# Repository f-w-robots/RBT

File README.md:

#### Installation
  - Install Arduino IDE 1.6.7+
  - To work with esp8266, install "Arduino core for ESP8266 WiFi chip", [2.3](https://github.com/esp8266/Arduino)
  - Libraries
    - [ArduinoWebSockets, our fork](https://github.com/f-w-robots/arduinoWebSockets)
    - [Arduino-IRremote](https://github.com/z3t0/Arduino-IRremote)
    - [MFRC522](https://github.com/miguelbalboa/rfid)

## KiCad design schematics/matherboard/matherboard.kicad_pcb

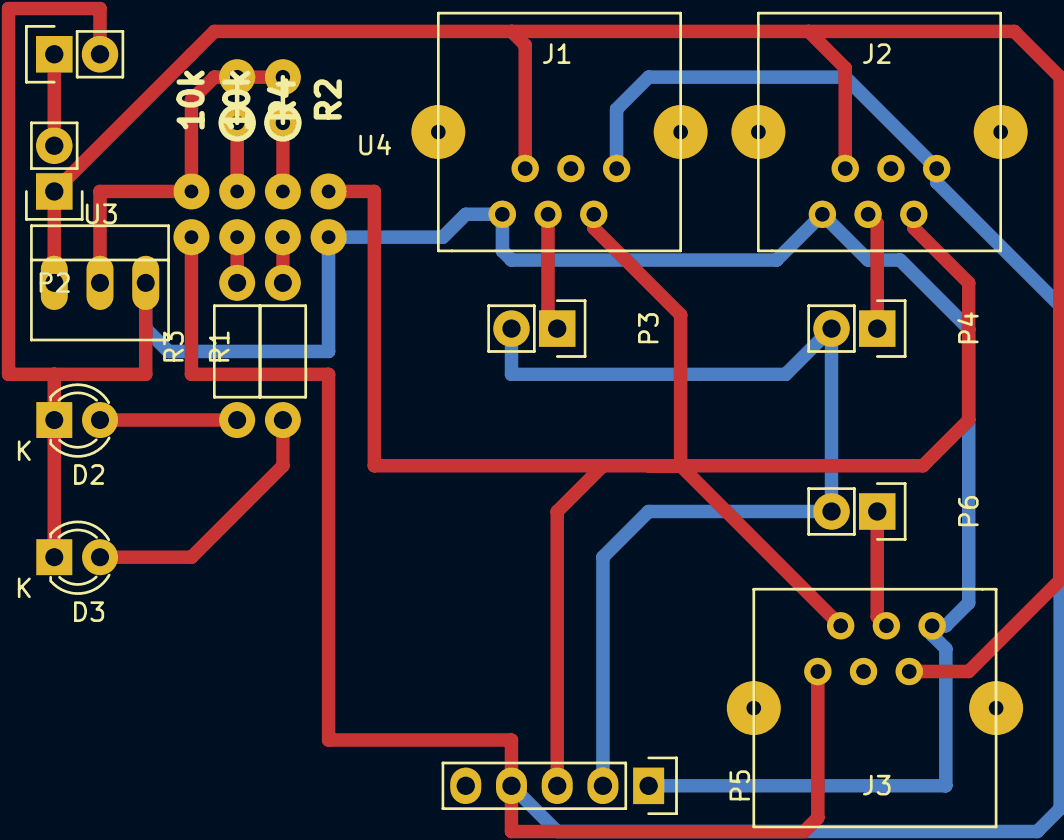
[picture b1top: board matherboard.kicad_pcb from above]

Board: 2 copper layers, 17 parts (0 on the bottom side), 16 nets.

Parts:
D2, D3: LED; LED-3MM
J1, J2, J3: RJ12; RJ12_E
P1: VCC/GND; Pin_Header_Straight_1x02
P2, P3, P4, P6: CONN_01X02; Pin_Header_Straight_1x02
P5: CONN_01X05; Pin_Header_Straight_1x05
R1, R3: 1k; Resistor_Horizontal_RM7mm
R2, R4: 10k; rc03_vert
U3: STAB3.3; PINHEAD1-3
U4: ESP8266; esp8266

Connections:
unnamed: D2.1, D3.1, J1.6, J2.6, J3.6, P1.2, P5.1, U3.3, U4.5
unnamed: D2.2, R3.1
unnamed: D3.2, R1.1
unnamed: J1.1, J2.1, J3.1, P5.4, U4.8
unnamed: J1.2, J2.2, J3.2, P5.3, U4.4
unnamed: J1.4, P3.1
unnamed: J1.5, J2.5, J3.5, P2.1, U3.1
unnamed: J2.4, P4.1
unnamed: J3.4, P6.1
unnamed: P1.1, P2.2
unnamed: P3.2, P4.2, P5.2, P6.2
unnamed: R1.2, U4.6
unnamed: R2.1, U4.3
unnamed: R2.2, R4.2, U3.2, U4.1
unnamed: R3.2, U4.7
unnamed: R4.1, U4.2

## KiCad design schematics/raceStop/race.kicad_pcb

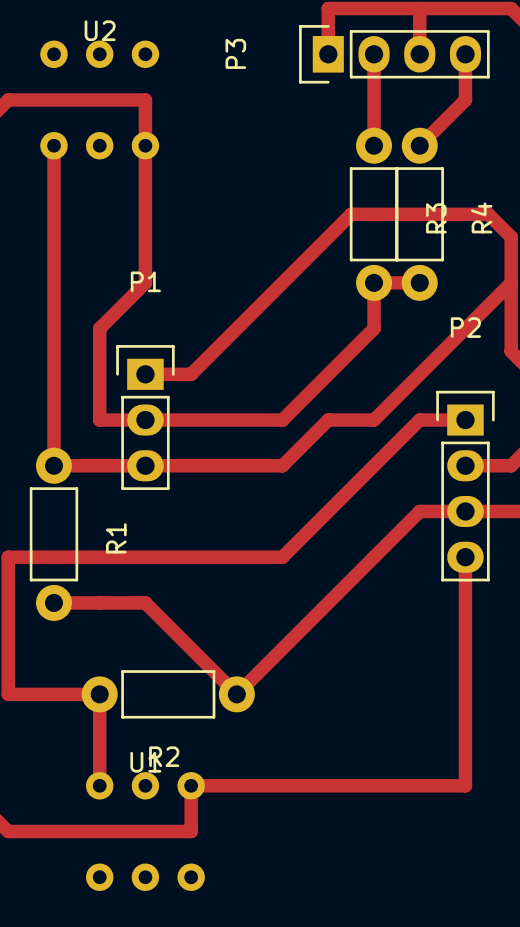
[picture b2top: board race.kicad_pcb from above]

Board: 2 copper layers, 9 parts (0 on the bottom side), 6 nets.

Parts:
P1: mass_start; Pin_Header_Straight_1x03
P2: VCC/GND/Start/Stop; Pin_Header_Straight_1x04
P3: LED; Pin_Header_Straight_1x04
R1, R2: 10k; Resistor_Horizontal_RM7mm
R3, R4: 200; Resistor_Horizontal_RM7mm
U1: STOP; button
U2: START; button

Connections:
unnamed: P1.1, P1.3, P2.2, R1.1, U2.4
unnamed: P1.2, P2.4, R3.2, R4.2, U1.3, U2.6
unnamed: P2.1, R2.2, U1.1
unnamed: P2.3, P3.1, P3.3, R1.2, R2.1
unnamed: P3.2, R3.1
unnamed: P3.4, R4.1

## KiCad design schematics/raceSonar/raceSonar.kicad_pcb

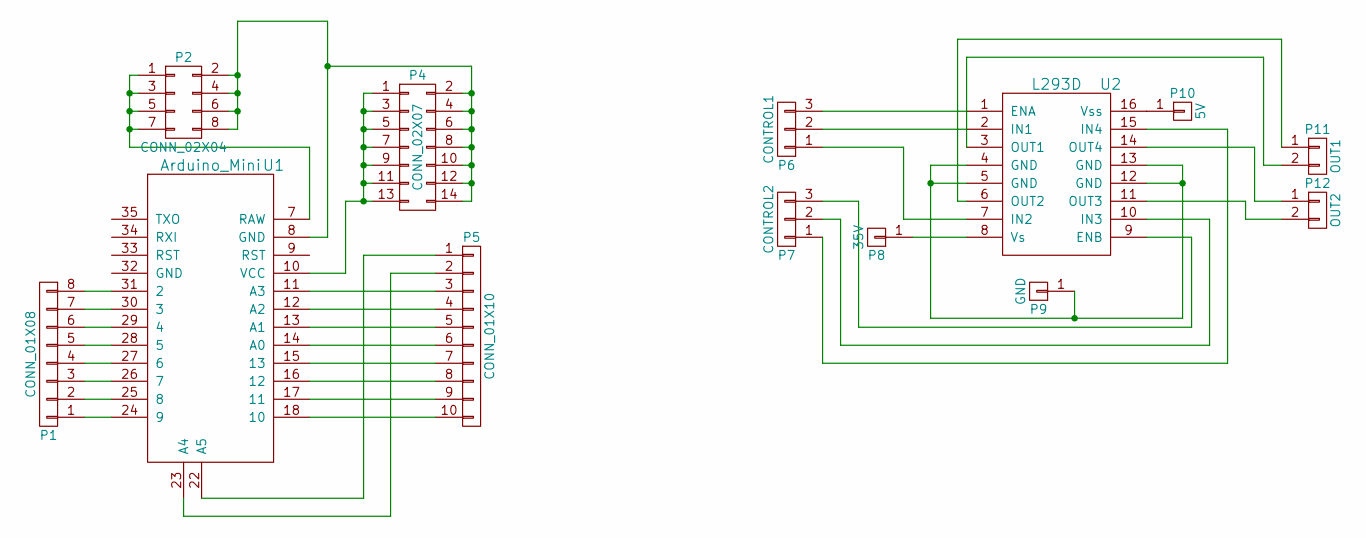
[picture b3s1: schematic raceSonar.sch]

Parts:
P1: CONN_01X08; Pin_Header_Straight_1x08
P2: CONN_02X04; Pin_Header_Straight_2x04
P4: CONN_02X07; Pin_Header_Straight_2x07
P5: CONN_01X10; Pin_Header_Straight_1x10
P6: CONTROL1; Pin_Header_Straight_1x03
P7: CONTROL2; Pin_Header_Straight_1x03
P8: 35V; Pin_Header_Straight_1x01
P9: GND; Pin_Header_Straight_1x01
P10: 5V; Pin_Header_Straight_1x01
P11: OUT1; Pin_Header_Straight_1x02
P12: OUT2; Pin_Header_Straight_1x02
U1: Arduino_Mini; arduino_mini_pro
U2: L293D; DIP-16_W7.62mm

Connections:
unnamed: P1.1, U1.24 (9)
unnamed: P1.2, U1.25 (8)
unnamed: P1.3, U1.26 (7)
unnamed: P1.4, U1.27 (6)
unnamed: P1.5, U1.28 (5)
unnamed: P1.6, U1.29 (4)
unnamed: P1.7, U1.30 (3)
unnamed: P1.8, U1.31 (2)
unnamed: P2.1, P2.3, P2.5, P2.7, U1.7 (RAW)
unnamed: P2.2, P2.4, P2.6, P2.8, P4.2, P4.4, P4.6, P4.8, P4.10, P4.12, P4.14, U1.8 (GND)
unnamed: P4.1, P4.3, P4.5, P4.7, P4.9, P4.11, P4.13, U1.10 (VCC)
unnamed: P5.1, U1.22 (A5)
unnamed: P5.2, U1.23 (A4)
unnamed: P5.3, U1.11 (A3)
unnamed: P5.4, U1.12 (A2)
unnamed: P5.5, U1.13 (A1)
unnamed: P5.6, U1.14 (A0)
unnamed: P5.7, U1.15 (13)
unnamed: P5.8, U1.16 (12)
unnamed: P5.9, U1.17 (11)
unnamed: P5.10, U1.18 (10)
unnamed: P6.1, U2.7 (IN2)
unnamed: P6.2, U2.2 (IN1)
unnamed: P6.3, U2.1 (ENA)
unnamed: P7.1, U2.15 (IN4)
unnamed: P7.2, U2.10 (IN3)
unnamed: P7.3, U2.9 (ENB)
unnamed: P8.1, U2.8 (Vs)
unnamed: P9.1, U2.4 (GND), U2.5 (GND), U2.12 (GND), U2.13 (GND)
unnamed: P10.1, U2.16 (Vss)
unnamed: P11.1, U2.6 (OUT2)
unnamed: P11.2, U2.3 (OUT1)
unnamed: P12.1, U2.14 (OUT4)
unnamed: P12.2, U2.11 (OUT3)

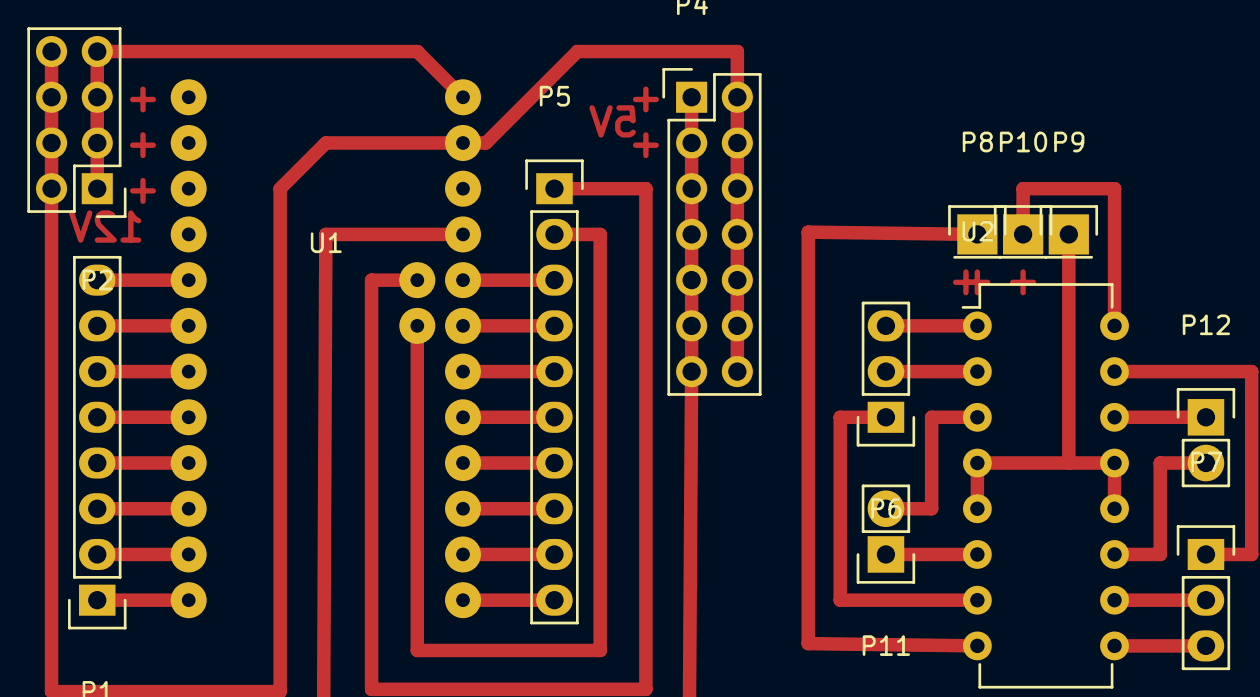
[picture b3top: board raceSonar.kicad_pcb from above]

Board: 2 copper layers, 13 parts (0 on the bottom side), 34 nets.

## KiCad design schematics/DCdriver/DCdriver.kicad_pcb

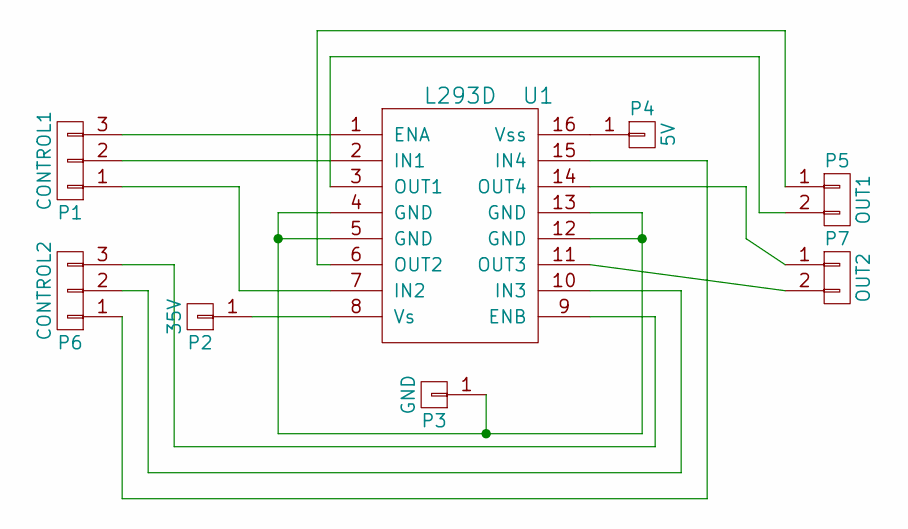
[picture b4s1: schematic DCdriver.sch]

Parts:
P1: CONTROL1; Pin_Header_Straight_1x03
P2: 35V; Pin_Header_Straight_1x01
P3: GND; Pin_Header_Straight_1x01
P4: 5V; Pin_Header_Straight_1x01
P5: OUT1; Pin_Header_Straight_1x02
P6: CONTROL2; Pin_Header_Straight_1x03
P7: OUT2; Pin_Header_Straight_1x02
U1: L293D; DIP-16_W7.62mm

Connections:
unnamed: P1.1, U1.7 (IN2)
unnamed: P1.2, U1.2 (IN1)
unnamed: P1.3, U1.1 (ENA)
unnamed: P2.1, U1.8 (Vs)
unnamed: P3.1, U1.4 (GND), U1.5 (GND), U1.12 (GND), U1.13 (GND)
unnamed: P4.1, U1.16 (Vss)
unnamed: P5.1, U1.6 (OUT2)
unnamed: P5.2, U1.3 (OUT1)
unnamed: P6.1, U1.15 (IN4)
unnamed: P6.2, U1.10 (IN3)
unnamed: P6.3, U1.9 (ENB)
unnamed: P7.1, U1.14 (OUT4)
unnamed: P7.2, U1.11 (OUT3)

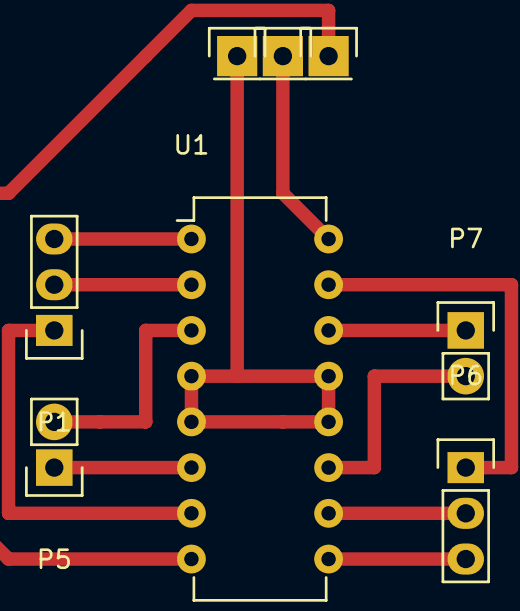
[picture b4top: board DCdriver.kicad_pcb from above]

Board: 2 copper layers, 8 parts (0 on the bottom side), 13 nets.

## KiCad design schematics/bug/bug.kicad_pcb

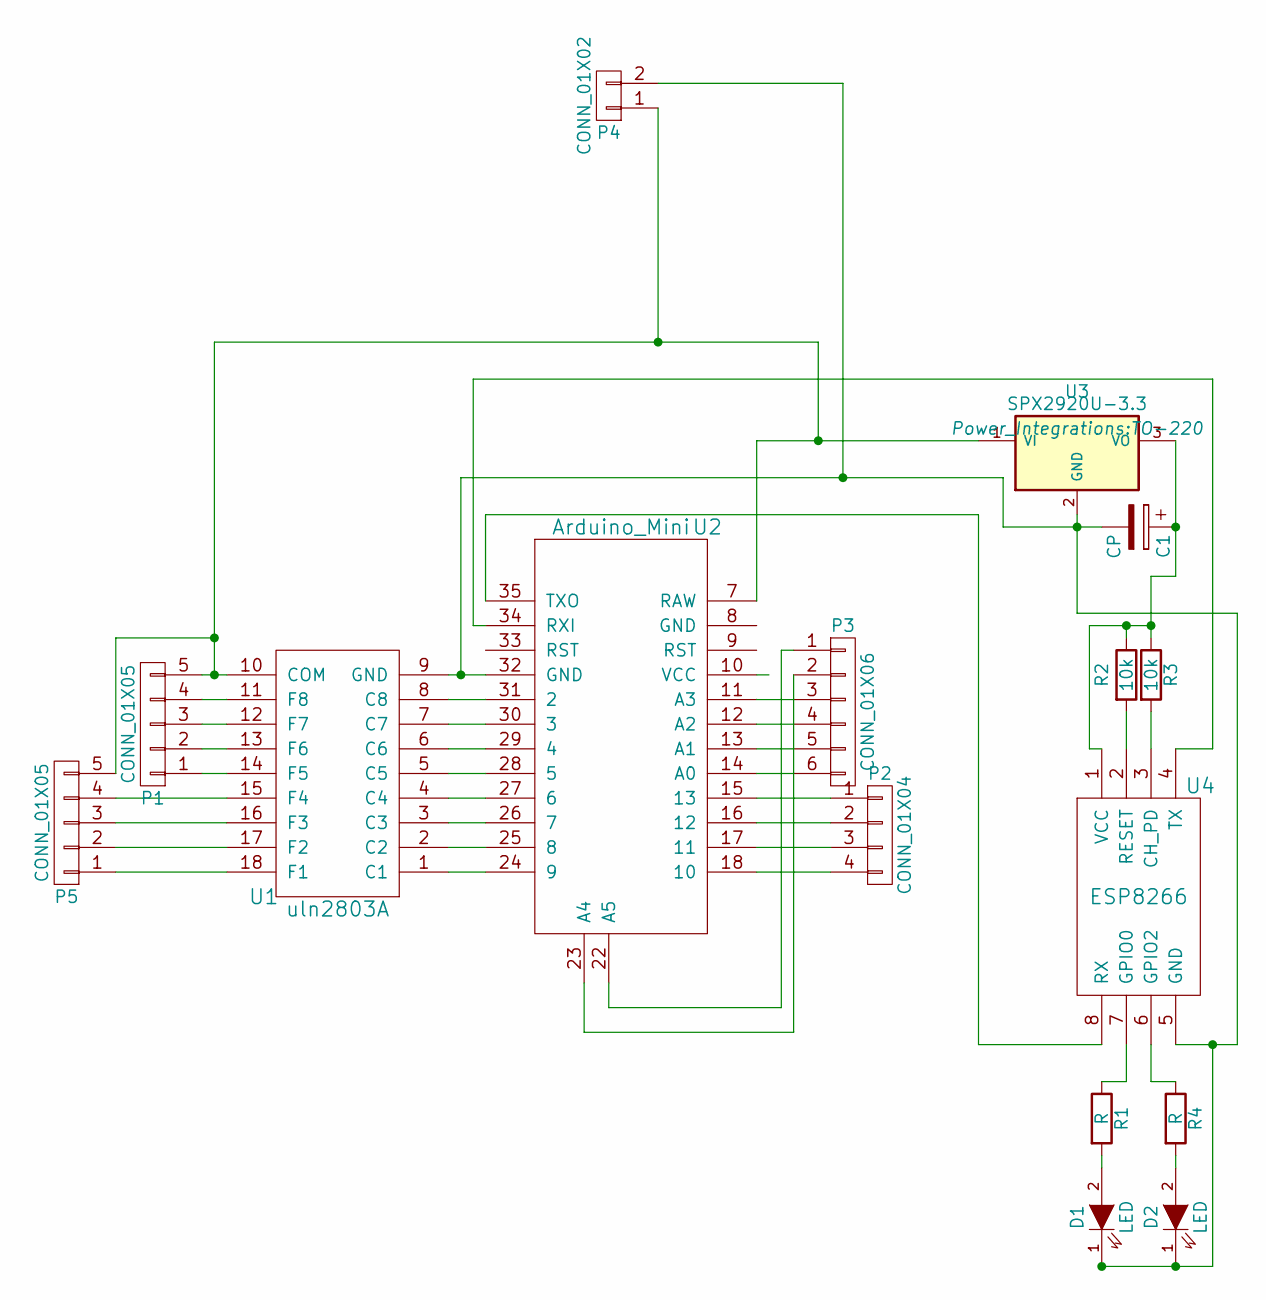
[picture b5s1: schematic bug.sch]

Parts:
C1: CP; CPR10X16
D1, D2: LED; LED-5MM
P1, P5: CONN_01X05; Pin_Header_Straight_1x05
P2: CONN_01X04; Pin_Header_Straight_1x04
P3: CONN_01X06; Pin_Header_Straight_1x06
P4: CONN_01X02; Pin_Header_Straight_1x02
R1, R4: R; rc05_vert
R2, R3: 10k; rc05_vert
U1: uln2803A; DIP-18_W7.62mm
U2: Arduino_Mini; arduino_mini_pro
U3: SPX2920U-3.3; TO-220
U4: ESP8266

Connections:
unnamed: C1.1, R2.1, R3.1, U3.3 (VO), U4.1 (VCC)
unnamed: C1.2, D1.1 (K), D2.1 (K), P4.2, U1.9 (GND), U2.32 (GND), U3.2 (GND), U4.5 (GND)
unnamed: D1.2 (A), R1.2
unnamed: D2.2 (A), R4.2
unnamed: P1.1, U1.14 (F5)
unnamed: P1.2, U1.13 (F6)
unnamed: P1.3, U1.12 (F7)
unnamed: P1.4, U1.11 (F8)
unnamed: P1.5, P4.1, P5.5, U1.10 (COM), U2.7 (RAW), U3.1 (VI)
unnamed: P2.1, U2.15 (13)
unnamed: P2.2, U2.16 (12)
unnamed: P2.3, U2.17 (11)
unnamed: P2.4, U2.18 (10)
unnamed: P3.1, U2.22 (A5)
unnamed: P3.2, U2.23 (A4)
unnamed: P3.3, U2.11 (A3)
unnamed: P3.4, U2.12 (A2)
unnamed: P3.5, U2.13 (A1)
unnamed: P3.6, U2.14 (A0)
unnamed: P5.1, U1.18 (F1)
unnamed: P5.2, U1.17 (F2)
unnamed: P5.3, U1.16 (F3)
unnamed: P5.4, U1.15 (F4)
unnamed: R1.1, U4.7 (GPIO0)
unnamed: R2.2, U4.2 (RESET)
unnamed: R3.2, U4.3 (CH_PD)
unnamed: R4.1, U4.6 (GPIO2)
unnamed: U1.1 (C1), U2.24 (9)
unnamed: U1.2 (С2), U2.25 (8)
unnamed: U1.3 (С3), U2.26 (7)
unnamed: U1.4 (С4), U2.27 (6)
unnamed: U1.5 (С5), U2.28 (5)
unnamed: U1.6 (С6), U2.29 (4)
unnamed: U1.7 (С7), U2.30 (3)
unnamed: U1.8 (С8), U2.31 (2)
unnamed: U2.34 (RXI), U4.4 (TX)
unnamed: U2.35 (TXO), U4.8 (RX)

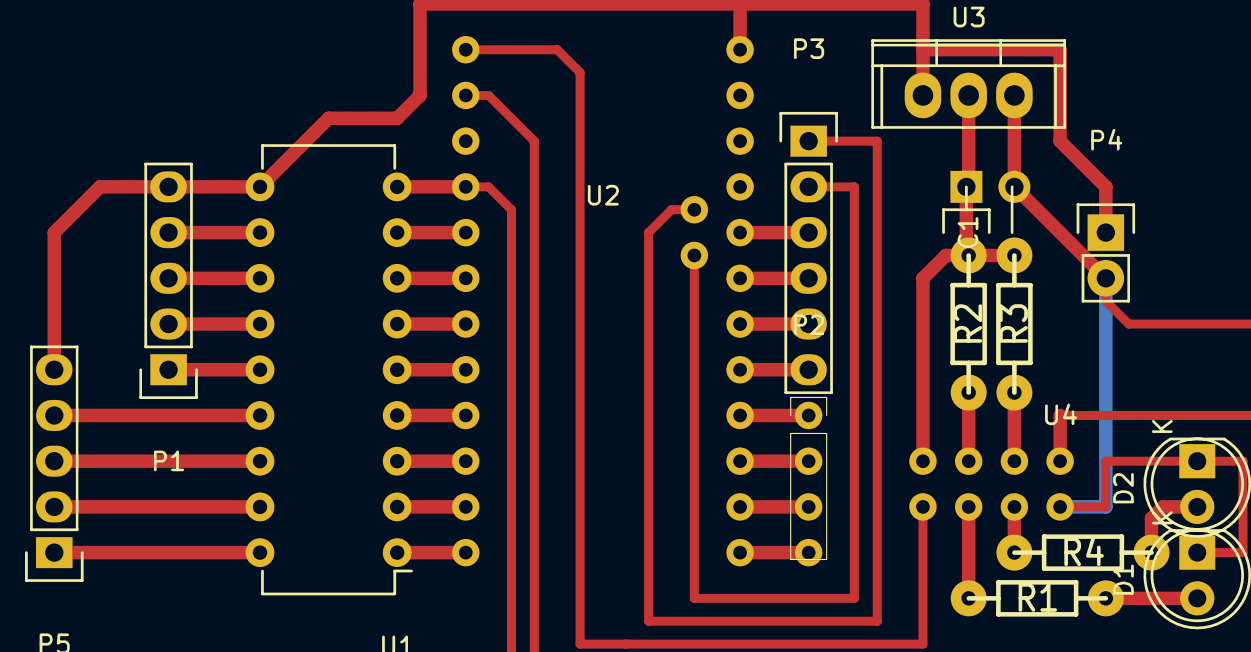
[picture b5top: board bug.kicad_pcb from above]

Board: 2 copper layers, 16 parts (0 on the bottom side), 37 nets.

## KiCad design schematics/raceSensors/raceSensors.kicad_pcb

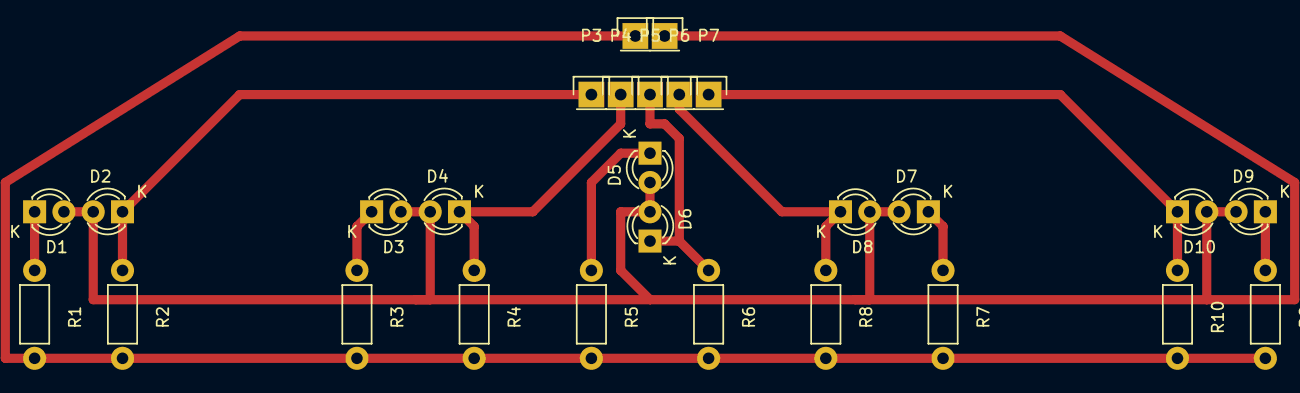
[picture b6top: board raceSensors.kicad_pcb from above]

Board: 2 copper layers, 27 parts (0 on the bottom side), 12 nets.

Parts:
D1, D2, D3, D4, D5, D6, D7, D8, D9, D10: LED; LED-3MM
P1, P2, P3, P4, P5, P6, P7: CONN_01X01; Pin_Header_Straight_1x01
R1, R3, R5, R7, R9: 150; Resistor_Horizontal_RM7mm
R2, R4, R6, R8, R10: 510k; Resistor_Horizontal_RM7mm

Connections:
unnamed: D1.1, R1.1
unnamed: D1.2, D2.2, D3.2, D4.2, D5.2, D6.2, D7.2, D8.2, D9.2, D10.2, P1.1
unnamed: D2.1, P3.1, R2.1
unnamed: D3.1, R3.1
unnamed: D4.1, P4.1, R4.1
unnamed: D5.1, R5.1
unnamed: D6.1, P5.1, R6.1
unnamed: D7.1, R7.1
unnamed: D8.1, P6.1, R8.1
unnamed: D9.1, R9.1
unnamed: D10.1, P7.1, R10.1
unnamed: P2.1, R1.2, R2.2, R3.2, R4.2, R5.2, R6.2, R7.2, R8.2, R9.2, R10.2

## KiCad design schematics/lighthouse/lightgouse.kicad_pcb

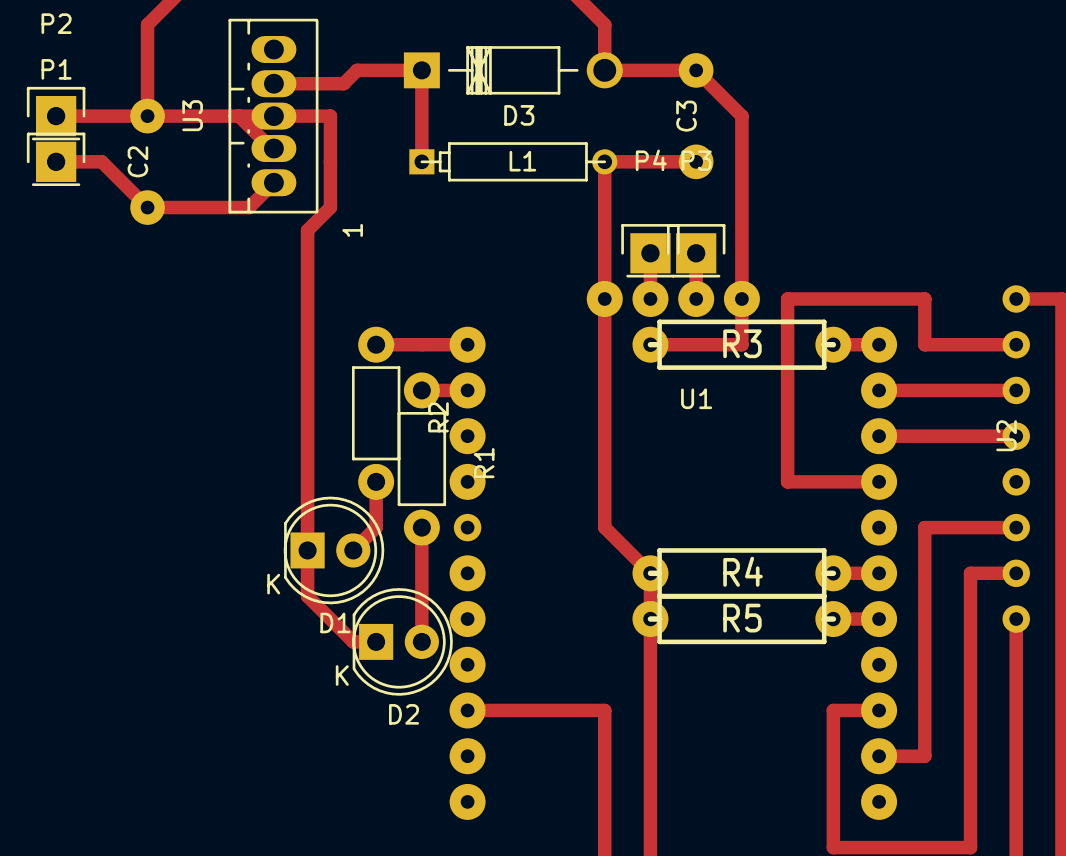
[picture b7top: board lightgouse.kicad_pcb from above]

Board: 2 copper layers, 18 parts (0 on the bottom side), 19 nets.

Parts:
C2: 100mkF; capasitor
C3: 1000mkF; capasitor
D1, D2: LED; LED-5MM
D3: D_Schottky; Diode_DO-41_SOD81_Horizontal_RM10
L1: 100mkH; CP4
P1: 3V3; Pin_Header_Straight_1x01
P2: GND; Pin_Header_Straight_1x01
P3: TX; Pin_Header_Straight_1x01
P4: RX; Pin_Header_Straight_1x01
R1, R2: 1k; Resistor_Horizontal_RM7mm
R3: 10K; RC05
R4, R5: 10k; RC05
U1: ESP-201; ESP201
U2: rc522; RC522
U3: LM2576; Pentawatt_Neutral_Straight_Vertical_TO220-5-T05A

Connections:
unnamed: C2.1, P1.1, U3.1
unnamed: C2.2, C3.2, D1.1, D2.1, D3.2, P2.1, R3.1, U1.4, U3.2, U3.3
unnamed: C3.1, L1.2, R4.1, R5.1, U1.1, U2.8
unnamed: D1.2, R2.2
unnamed: D2.2, R1.2
unnamed: D3.1, L1.1, U3.4
unnamed: P3.1, U1.3
unnamed: P4.1, U1.2
unnamed: R1.1, U1.6
unnamed: R2.1, U1.5
unnamed: R3.2, U1.26
unnamed: R4.2, U1.21
unnamed: R5.2, U1.20
unnamed: U1.13, U2.1
unnamed: U1.17, U2.6
unnamed: U1.18, U2.7
unnamed: U1.23, U2.2
unnamed: U1.24, U2.4
unnamed: U1.25, U2.3

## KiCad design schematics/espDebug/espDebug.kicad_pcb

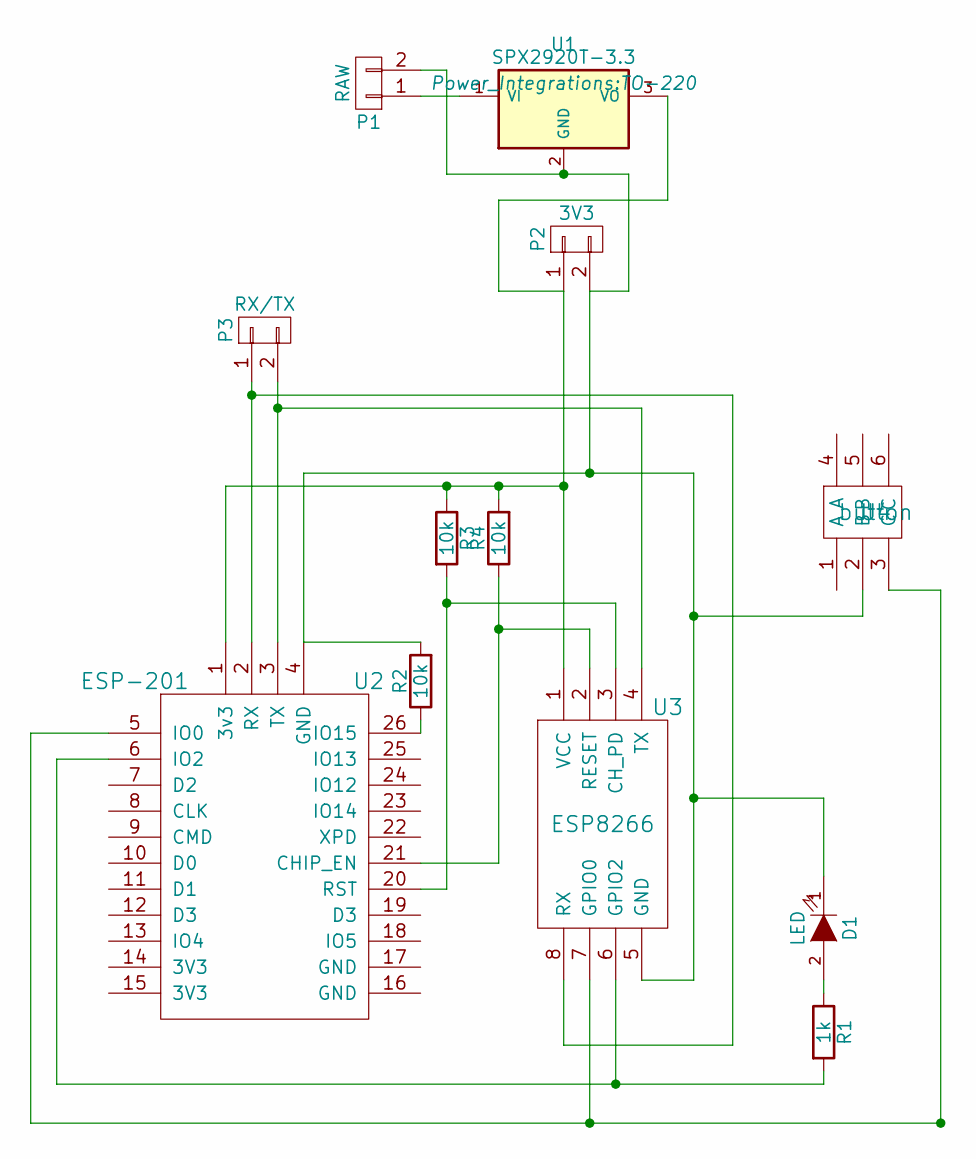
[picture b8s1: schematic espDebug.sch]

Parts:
D1: LED; LED-3MM
P1: RAW; Pin_Header_Straight_1x02
P2: 3V3; Pin_Header_Straight_1x02
P3: RX/TX; Pin_Header_Straight_1x02
R1: 1k; Resistor_Horizontal_RM7mm
R2, R3, R4: 10k; Resistor_Horizontal_RM7mm
U1: SPX2920T-3.3; TO-220
U2: ESP-201; ESP201
U3: ESP8266; esp8266
U4: button

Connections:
unnamed 0: D1.1 (K), P1.2, P2.2, R2.2, U1.2 (GND), U2.4 (GND), U3.5 (GND), U4.2 (B); also elsewhere on the board
unnamed: D1.2 (A), R1.1
unnamed: P1.1, U1.1 (VI)
unnamed: P2.1, R3.1, R4.2, U1.3 (VO), U2.1 (3v3), U3.1 (VCC)
unnamed: P3.1, U2.2 (RX), U3.8 (RX)
unnamed: P3.2, U2.3 (TX), U3.4 (TX)
unnamed: R1.2, U2.6 (IO2), U3.6 (GPIO2)
unnamed: R2.1, U2.26 (IO15)
unnamed: R3.2, U2.20 (RST), U3.3 (CH_PD)
unnamed: R4.1, U2.21 (CHIP_EN), U3.2 (RESET)
unnamed 11: U2.5 (IO0), U3.7 (GPIO0), U4.3 (C); also elsewhere on the board

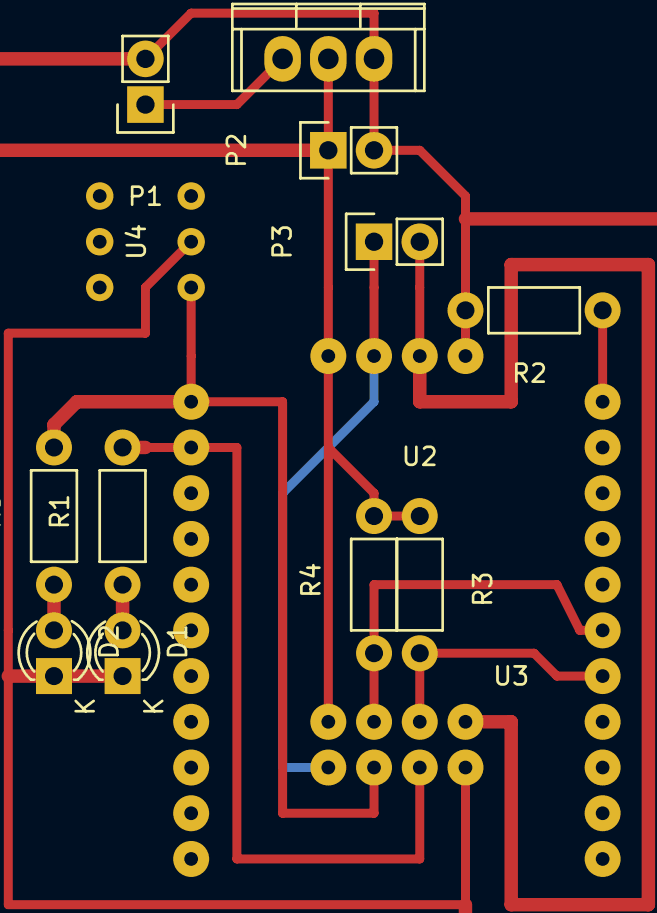
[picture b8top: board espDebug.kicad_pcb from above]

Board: 2 copper layers, 14 parts (0 on the bottom side), 12 nets.

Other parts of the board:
D2: LED; LED-3MM
R5: 1k; Resistor_Horizontal_RM7mm

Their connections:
unnamed 0: D2.1; also elsewhere on the board
unnamed: D2.2, R5.1
unnamed 11: R5.2; also elsewhere on the board

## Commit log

2016-02-24 Move the arduino code here
2016-02-28 Update LineSensor algorithm
2016-02-28 Added 28BYJ-48 support
2016-02-28 Small update esp8266 firmware
2016-02-28 Use Stepper Motors as engines
2016-02-28 Use Serial instead SoftwareSerial for ESP8266
2016-02-28 MotorDriver
2016-02-29 Update Arduino for ESP and esp websockets libraries
2016-02-29 Use step engines for ultrasonicx
2016-02-29 Update ultrasonic code for stepper motor
2016-02-29 Separate sketch for stepper car motor car
2016-02-29 ultrasonicStepper follow for line
2016-02-29 ESP8266 for ultrasonicStepper
2016-03-03 Added esp8266I2C
2016-03-03 Ultrasonic by new protocol
2016-03-03 Stepper support in ultrasonicI2C
2016-03-03 Full messages exchange on i2c support
2016-03-03 Add timeline debug to esp
2016-03-03 Increase serrial speed
2016-03-04 Add LED indication to esp8266 I2C
2016-03-04 Optimize ultrasonicI2C code
2016-03-04 Rewrite init package
2016-03-04 Use startResponse and format code
2016-03-04 Added site to package
2016-03-05 Add code for calibration sensors
2016-03-05 Fix stop bug in 28byj
2016-03-05 Fix direction and sensors reading in car
2016-03-05 Remove debug packages from esp8266
2016-03-05 Fix bug on sensors reading
2016-03-07 Repeat connect to wifi after 10 seconds fail
2016-03-09 Reset connection only if wifi has status failed
2016-03-10 Remove legacy projects
2016-03-11 Added commands for calibration
2016-03-11 Small fixes
2016-03-11 Remove unnesessary println
2016-03-16 Schema for LineSensors
2016-03-16 Update LineSensor schematic
2016-03-18 Add ESP8266 schematic
2016-03-22 Update eps8266 schematic
2016-03-22 Remove cd4051 from sensors and add led debug to arduino
2016-03-24 Fix calibration bug
2016-03-24 Added schematic for bug
2016-03-29 Sensors+ESP+Arduino schematic
2016-04-02 set input pins for BUG
2016-04-02 Update ip and id for esp
2016-04-02 Update schematic lineSensor and bug
2016-04-04 SCHEMATICS: group output pins
2016-04-04 SCHEMATICS: move arduino A4 and A5 pins
2016-04-05 BUG: fix bug with left wheel
2016-04-05 BUG: fix electricity consumption on stop
2016-04-07 Support for arduino 3v3 and simplify MotorDriver code
2016-04-07 SCHEMATIC: move button and led to one place
2016-04-08 SCHEMATIC: update lineSensors and bug
2016-04-09 Set serial speed to 115200
2016-04-09 Cleanup repository
2016-04-11 Add final symbol to package
2016-04-12 BUG: change debug led13 appointment
2016-04-12 Added PING-PONG to esp8266 and debug package reciving
2016-04-13 Rewrite lineSensors scheme and small update bug
2016-04-14 Sipmlify esp8266 code
2016-04-14 Fix esp8266 not response bug
2016-04-17 Update schematic
2016-04-21 RFID for esp8266
2016-04-21 SCHEMATIC: create scheme lighthouse
2016-04-21 Remove VirtualDevice from esp
2016-04-22 Save ESP8266 config to EEPROM
2016-04-22 ESP8266 - load config from lighthouse
2016-04-23 LightHouse: support RFID
2016-04-23 espDebug scheme
2016-04-23 lighthouse scheme
2016-04-23 lighthouse
2016-04-23 Binary websockets in hardware
2016-04-23 update lighthouse
2016-04-23 lighthouse schematic update
2016-04-25 Update bugDebug schematic
2016-04-25 Fixes for lighthouse
2016-04-25 Fix lighthouse bugs
2016-04-28 ESP always connect to lighthouse
2016-04-28 Lighthouse now if fully work
2016-04-29 Fix lighthouse if not wifi available
2016-04-30 BUG: send whiskers values
2016-04-30 Update schematics for whiskers
2016-05-02 SCHEMATICS: prepare Lighthouse for production
2016-05-02 Refactoring
2016-05-02 Fix esp8266 code after refactroring
2016-05-02 Lighthouse and esp8266 refactoring
2016-05-03 Update lineSensor board for sonar power
2016-05-04 SCHMATIC: Update espDebug
2016-05-07 Add SR04 to BUG
2016-05-07 raceSensors
2016-05-07 Update bug schematic
2016-05-07 Try fix lighthouse
2016-05-08 DCdriver schematic
2016-05-13 Update SR04
2016-05-13 Add race
2016-05-17 SCHEMATICS:RJ-matherboard, race sonar and stepper Driver
2016-05-17 Remove USBtoTTL from matherboard
2016-05-21 Race algorithm by Alexander Tsed
2016-05-22 update1
2016-05-23 Schematic
2016-05-25 Move schematics to another repo
2016-06-09 SPI test
2016-06-13 SPI matherboard
2016-06-15 SPI update
2016-06-28 New Wheels Driver
2016-06-28 Update NotDriver
2016-06-29 NotDriver in style as Driver
2016-06-29 Add many modules for drivers
2016-06-29 Fix outPut bug in driver
2016-06-29 Reorganize files storage
2016-07-01 Fix DCDriver
2016-07-01 Add module number for output eps8266 packages
2016-07-01 Fix Driver packages bug
2016-07-02 Some fixes in driver
2016-07-04 Increase spi speed and fix crash
2016-07-04 Fix crash if recieved byte greater then 127
2016-07-04 Support up to four bytes for response in Driver
2016-07-04 Added RobatzIR modules
2016-07-30 update password
2016-09-12 ESP8266 IR
2016-09-12 Saturday
2016-10-31 IRRawReciver
2016-11-01 Read 433
2016-11-02 Create Class for raw read ir
2016-11-02 Update IRRawReciver
2016-11-02 Recive 433Mhz signal
2016-11-02 RawSend
2017-02-05 EduKitLight
2017-02-13 Released code for EduKitLIght
